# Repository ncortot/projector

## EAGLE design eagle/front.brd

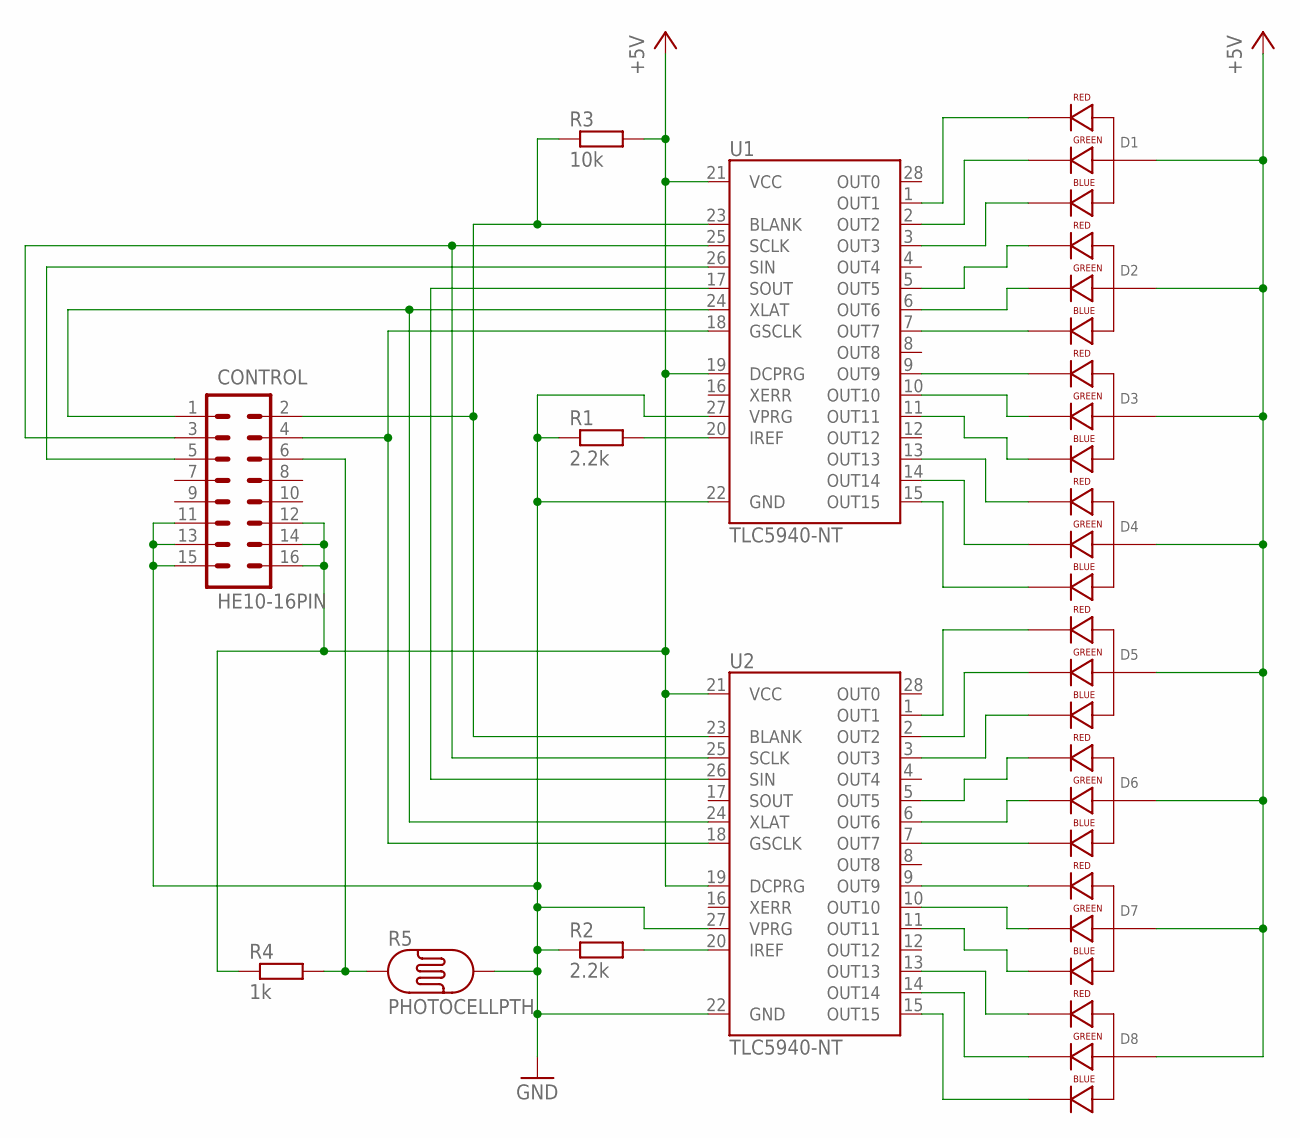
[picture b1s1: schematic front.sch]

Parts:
CONTROL: HE10-16PIN; HE10-16
D1, D2, D3, D4, D5, D6, D7, D8: LED-RGB-CA-THRUCLEAR; LED-RGB-THRU
R1, R2: 2.2k; M1206
R3: 10k; M1206
R4: 1k; M1206
R5: PHOTOCELLPTH; PHOTOCELL
U1, U2: TLC5940-NT; DIL28-3

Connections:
+5V: CONTROL.12, CONTROL.14, CONTROL.16, D1.2 (ANODE), D2.2 (ANODE), D3.2 (ANODE), D4.2 (ANODE), D5.2 (ANODE), D6.2 (ANODE), D7.2 (ANODE), D8.2 (ANODE), R3.2, R4.1, U1.19 (DCPRG), U1.21 (VCC), U2.19 (DCPRG), U2.21 (VCC)
GND: CONTROL.11, CONTROL.13, CONTROL.15, R1.1, R2.1, R5.2, U1.22 (GND), U1.27 (VPRG), U2.22 (GND), U2.27 (VPRG)
unnamed: D1.1 (RED_CATHODE), U1.1 (OUT1)
unnamed: D1.3 (GREEN_CATHODE), U1.2 (OUT2)
unnamed: D1.4 (BLUE_CATHODE), U1.3 (OUT3)
unnamed: D2.4 (BLUE_CATHODE), U1.7 (OUT7)
unnamed: D2.3 (GREEN_CATHODE), U1.6 (OUT6)
unnamed: D2.1 (RED_CATHODE), U1.5 (OUT5)
unnamed: D3.1 (RED_CATHODE), U1.9 (OUT9)
unnamed: D3.3 (GREEN_CATHODE), U1.10 (OUT10)
unnamed: D3.4 (BLUE_CATHODE), U1.11 (OUT11)
unnamed: D4.1 (RED_CATHODE), U1.13 (OUT13)
unnamed: D4.3 (GREEN_CATHODE), U1.14 (OUT14)
unnamed: D4.4 (BLUE_CATHODE), U1.15 (OUT15)
unnamed: D5.1 (RED_CATHODE), U2.1 (OUT1)
unnamed: D5.3 (GREEN_CATHODE), U2.2 (OUT2)
unnamed: D5.4 (BLUE_CATHODE), U2.3 (OUT3)
unnamed: D6.1 (RED_CATHODE), U2.5 (OUT5)
unnamed: D6.3 (GREEN_CATHODE), U2.6 (OUT6)
unnamed: D6.4 (BLUE_CATHODE), U2.7 (OUT7)
unnamed: D7.1 (RED_CATHODE), U2.9 (OUT9)
unnamed: D7.3 (GREEN_CATHODE), U2.10 (OUT10)
unnamed: D7.4 (BLUE_CATHODE), U2.11 (OUT11)
unnamed: D8.1 (RED_CATHODE), U2.13 (OUT13)
unnamed: D8.3 (GREEN_CATHODE), U2.14 (OUT14)
unnamed: D8.4 (BLUE_CATHODE), U2.15 (OUT15)
unnamed: U1.17 (SOUT), U2.26 (SIN)
unnamed: R1.2, U1.20 (IREF)
unnamed: R2.2, U2.20 (IREF)
unnamed: CONTROL.5, U1.26 (SIN)
unnamed: CONTROL.2, R3.1, U1.23 (BLANK), U2.23 (BLANK)
unnamed: CONTROL.3, U1.25 (SCLK), U2.25 (SCLK)
unnamed: CONTROL.1, U1.24 (XLAT), U2.24 (XLAT)
unnamed: CONTROL.4, U1.18 (GSCLK), U2.18 (GSCLK)
unnamed: CONTROL.6, R4.2, R5.1

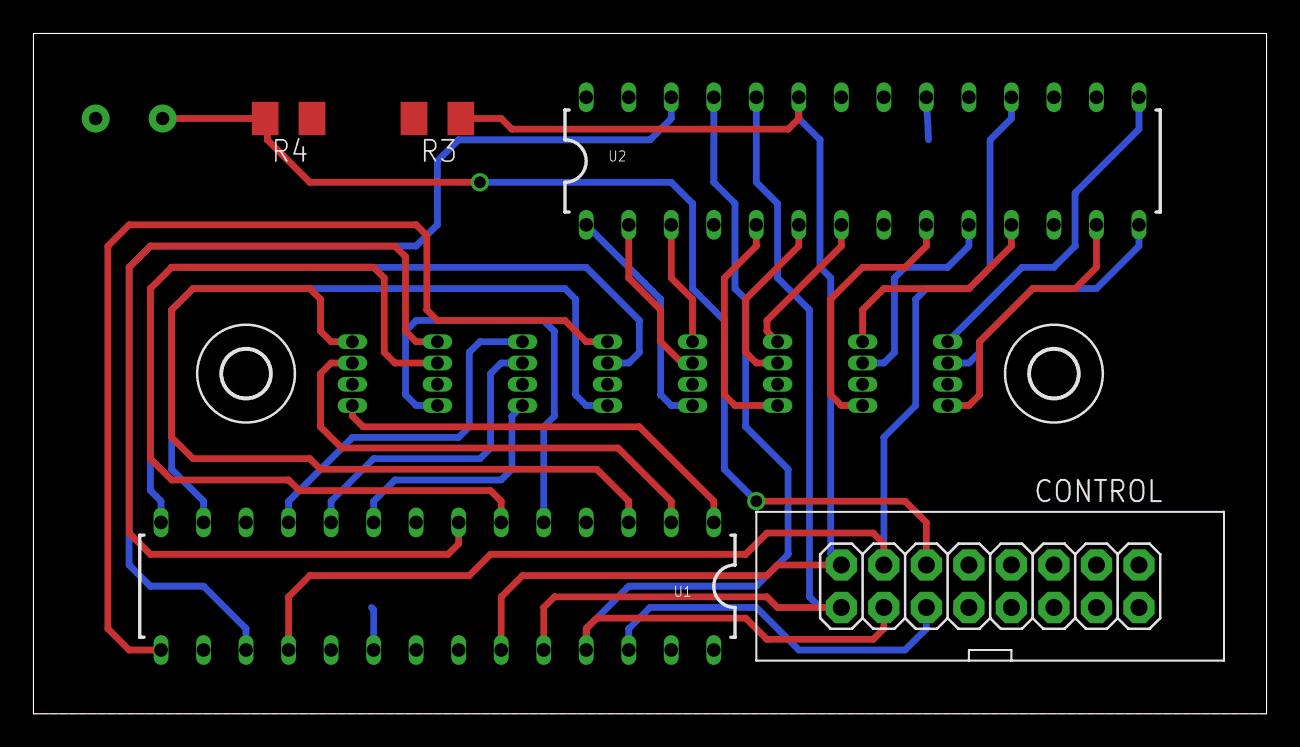
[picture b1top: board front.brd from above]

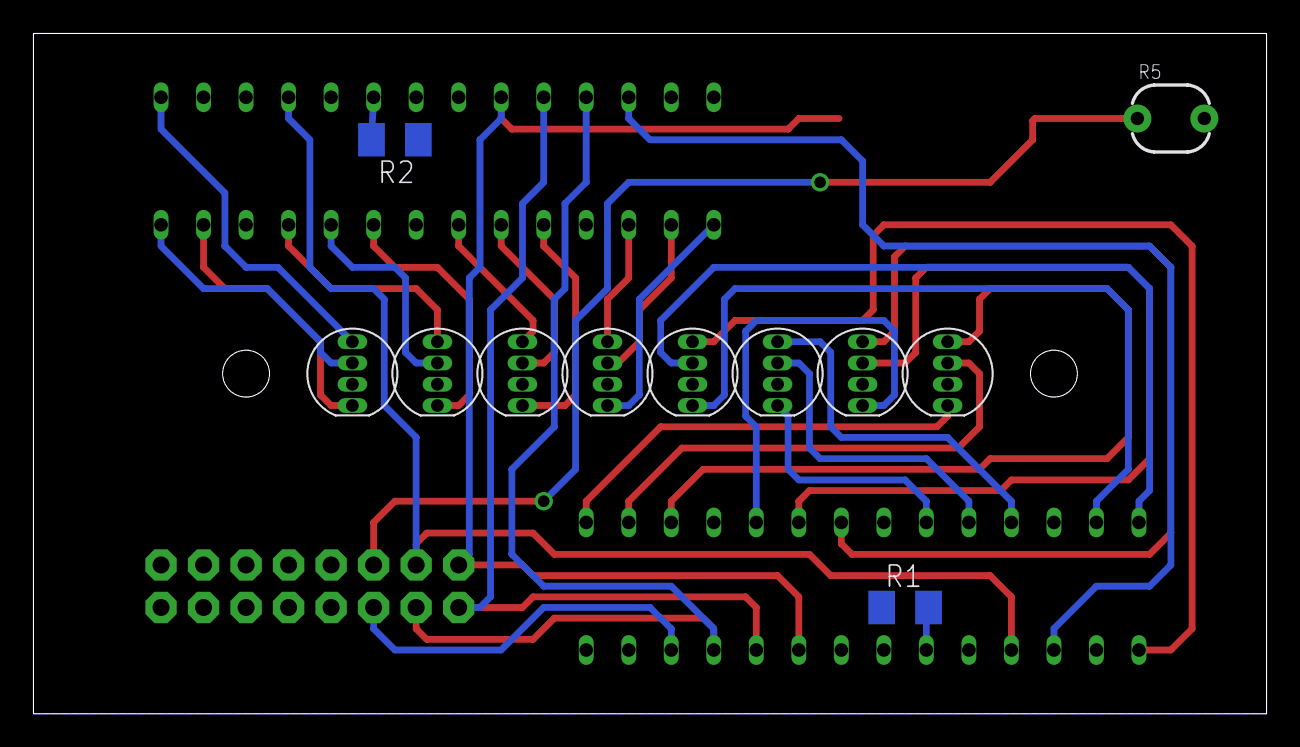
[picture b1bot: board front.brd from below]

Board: 2 copper layers, 73.7 x 40.6 mm, 18 parts (11 on the bottom side), 35 nets.

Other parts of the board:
U$1, U$2: 2,8

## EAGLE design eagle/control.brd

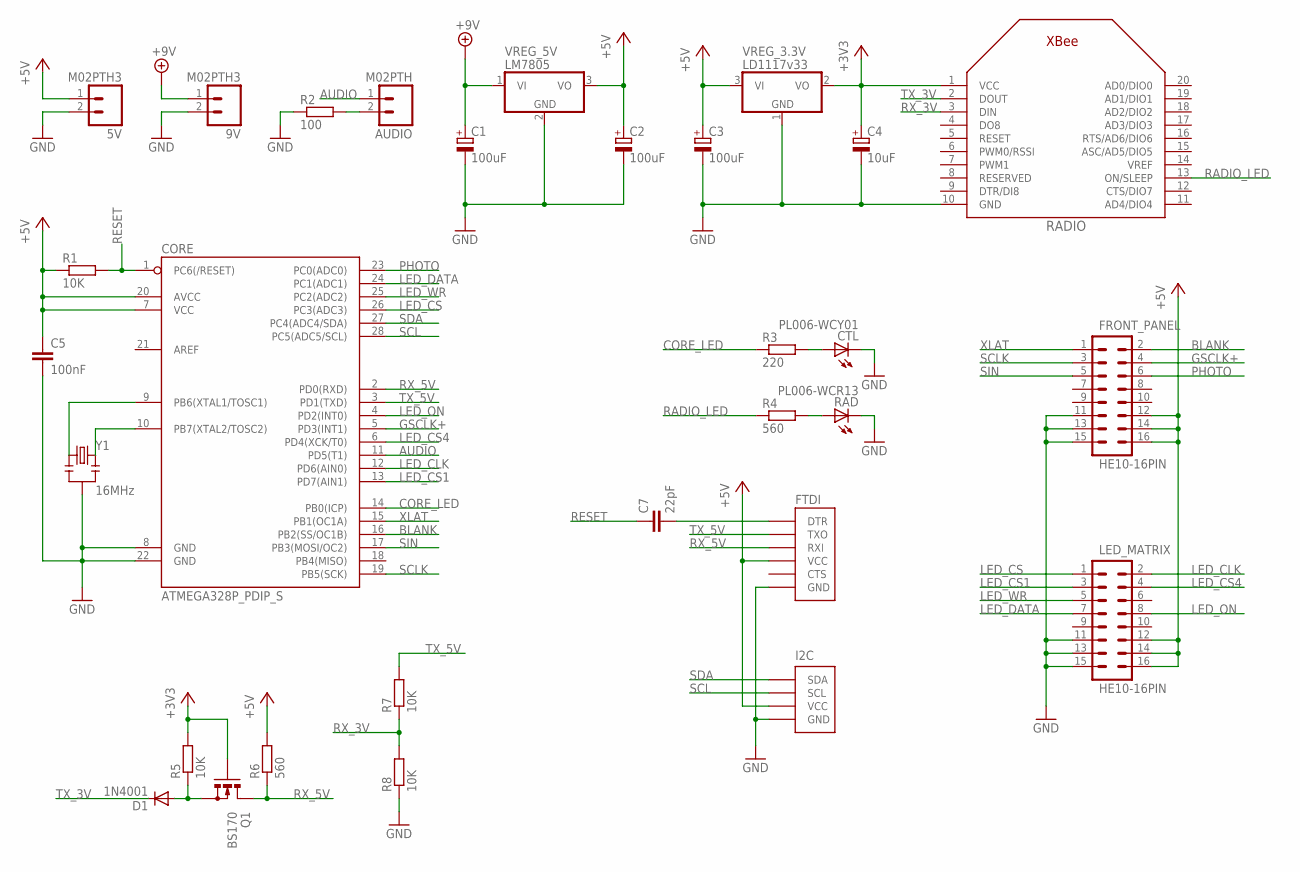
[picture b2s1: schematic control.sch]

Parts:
5V, 9V: M02PTH3; 1X02_LONGPADS
AUDIO: M02PTH; 1X02
C1, C2, C3: 100uF; E2,5-6E
C4: 10uF; E2-5
C5: 100nF; C050-024X044
C7: 22pF; C050-024X044
CORE: ATMEGA328P_PDIP_S; SOCKET-28-3
CTL: PL006-WCY01; SOT23
D1: 1N4001; DIODE-1N4001
FRONT_PANEL: HE10-16PIN; HE10-16
FTDI: FTDI_DEVICE; FTDI_DEVICE_SIDE
I2C: I2C_DEVICE; I2C_DEVICE_SIDE
LED_MATRIX: HE10-16PIN; HE10-16
Q1: BS170; SOT54E
R1, R5, R7, R8: 10K; M1206
R2: 100; 0204/7
R3: 220; M1206
R4, R6: 560; M1206
RAD: PL006-WCR13; SOT23
RADIO: XBEE
VREG_3.3V: LD1117v33; TO220H
VREG_5V: LM7805; TO220H
Y1: 16MHz; RESONATOR-PTH

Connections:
+3V3: C4.+, Q1.G, R5.2, RADIO.1 (VCC), VREG_3.3V.2 (VO)
+5V: 5V.1, C2.+, C3.+, C5.1, CORE.7 (VCC), CORE.20 (AVCC), FRONT_PANEL.12, FRONT_PANEL.14, FRONT_PANEL.16, FTDI.P$4 (VCC), I2C.P$4 (VCC), LED_MATRIX.12, LED_MATRIX.14, LED_MATRIX.16, R1.1, R6.2, VREG_3.3V.3 (VI), VREG_5V.3 (VO)
+9V: 9V.1, C1.+, VREG_5V.1 (VI)
AUDIO: AUDIO.1, CORE.11 (PD5(T1))
BLANK: CORE.16 (PB2(SS/OC1B)), FRONT_PANEL.2
CORE_LED: CORE.14 (PB0(ICP)), R3.1
GND: 5V.2, 9V.2, C1.-, C2.-, C3.-, C4.-, C5.2, CORE.8 (GND), CORE.22 (GND), CTL.3 (C), FRONT_PANEL.11, FRONT_PANEL.13, FRONT_PANEL.15, FTDI.P$6 (GND), I2C.P$6 (GND), LED_MATRIX.11, LED_MATRIX.13, LED_MATRIX.15, R2.1, R8.1, RAD.3 (C), RADIO.10 (GND), VREG_3.3V.1 (GND), VREG_5V.2 (GND), Y1.2
GSCLK+: CORE.5 (PD3(INT1)), FRONT_PANEL.4
LED_CLK: CORE.12 (PD6(AIN0)), LED_MATRIX.2
LED_CS: CORE.26 (PC3(ADC3)), LED_MATRIX.1
LED_CS1: CORE.13 (PD7(AIN1)), LED_MATRIX.3
LED_CS4: CORE.6 (PD4(XCK/T0)), LED_MATRIX.4
LED_DATA: CORE.24 (PC1(ADC1)), LED_MATRIX.7
LED_ON: CORE.4 (PD2(INT0)), LED_MATRIX.8
LED_WR: CORE.25 (PC2(ADC2)), LED_MATRIX.5
unnamed: AUDIO.2, R2.2
unnamed: D1.A, Q1.S, R5.1
unnamed: CORE.10 (PB7(XTAL2/TOSC2)), Y1.3
unnamed: CORE.9 (PB6(XTAL1/TOSC1)), Y1.1
unnamed: C7.2, FTDI.P$1 (DTR)
unnamed: CTL.1 (A), R3.2
unnamed: R4.2, RAD.1 (A)
PHOTO: CORE.23 (PC0(ADC0)), FRONT_PANEL.6
RADIO_LED: R4.1, RADIO.13 (ON/SLEEP)
RESET: C7.1, CORE.1 (PC6(/RESET)), R1.2
RX_3V: R7.1, R8.2, RADIO.3 (DIN)
RX_5V: CORE.2 (PD0(RXD)), FTDI.P$3 (RXI), Q1.D, R6.1
SCL: CORE.28 (PC5(ADC5/SCL)), I2C.P$2 (SCL)
SCLK: CORE.19 (PB5(SCK)), FRONT_PANEL.3
SDA: CORE.27 (PC4(ADC4/SDA)), I2C.P$1 (SDA)
SIN: CORE.17 (PB3(MOSI/OC2)), FRONT_PANEL.5
TX_3V: D1.C, RADIO.2 (DOUT)
TX_5V: CORE.3 (PD1(TXD)), FTDI.P$2 (TXO), R7.2
XLAT: CORE.15 (PB1(OC1A)), FRONT_PANEL.1

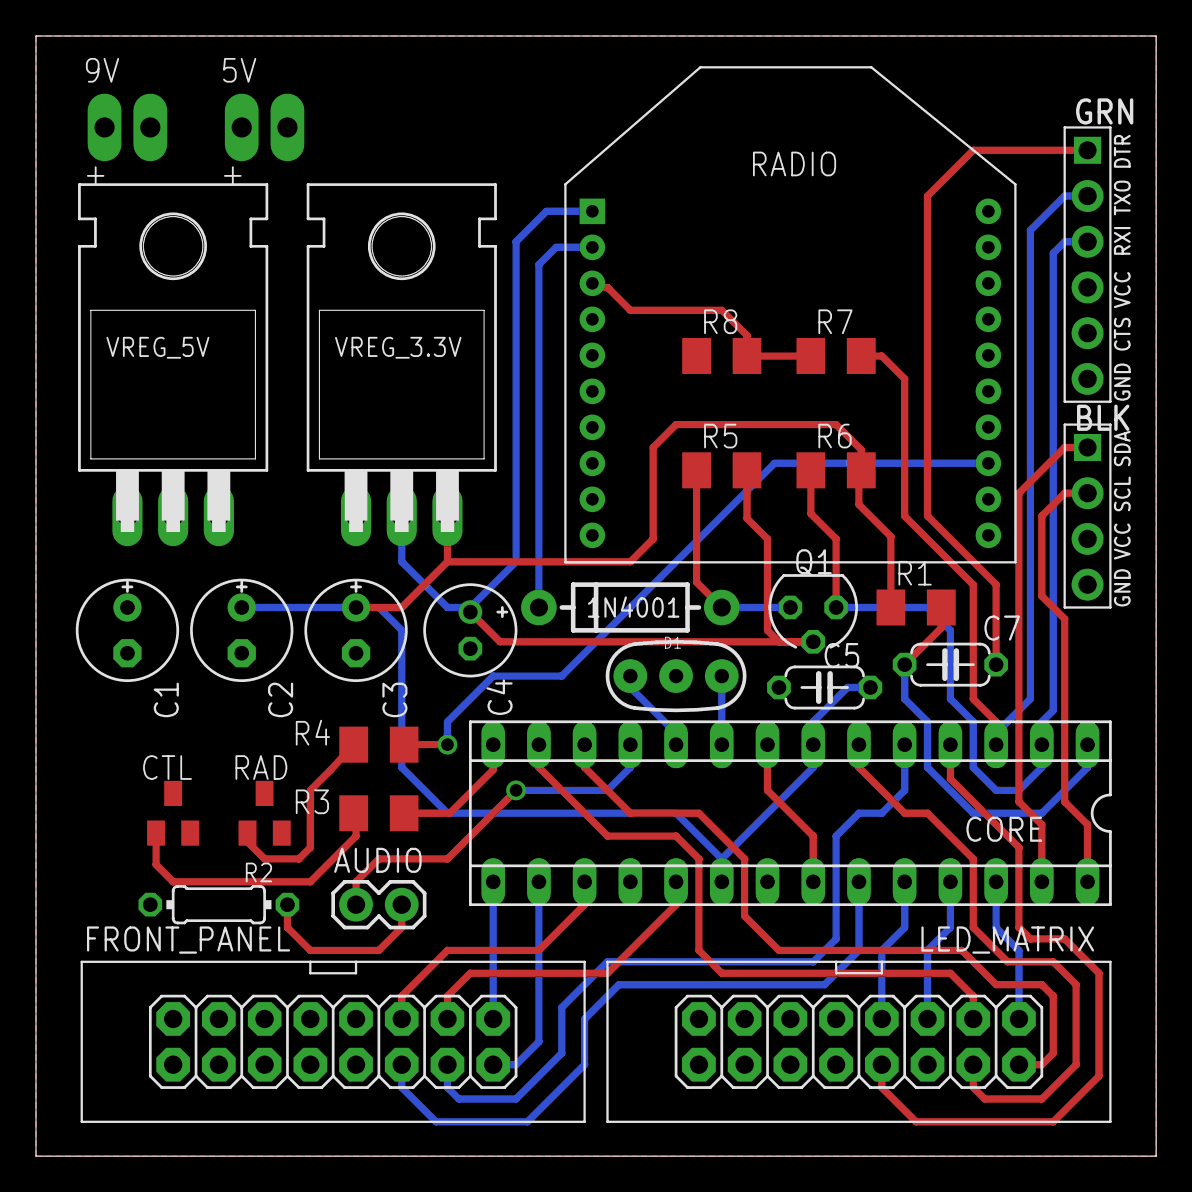
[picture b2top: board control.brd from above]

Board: 2 copper layers, 62.2 x 62.2 mm, 30 parts (0 on the bottom side), 34 nets.

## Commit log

2013-09-30 Scematics & boards v1
2013-09-30 Add board testing code
2013-10-28 Simple testing code for new Yun hardware
2013-10-28 Better KIT display
2013-10-28 Refactor arguments parsing
2014-04-01 Eagle schematics upgrade
2014-04-01 Remove obsolete code
2014-08-15 Build the Arduino project using a Makefile
2014-08-15 Audio sample player

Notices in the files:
parts and their libraries:
SparkFun-FreqCtrl: Licensing: CC v3.0 Share-Alike You are welcome to use this library for commercial purposes.
